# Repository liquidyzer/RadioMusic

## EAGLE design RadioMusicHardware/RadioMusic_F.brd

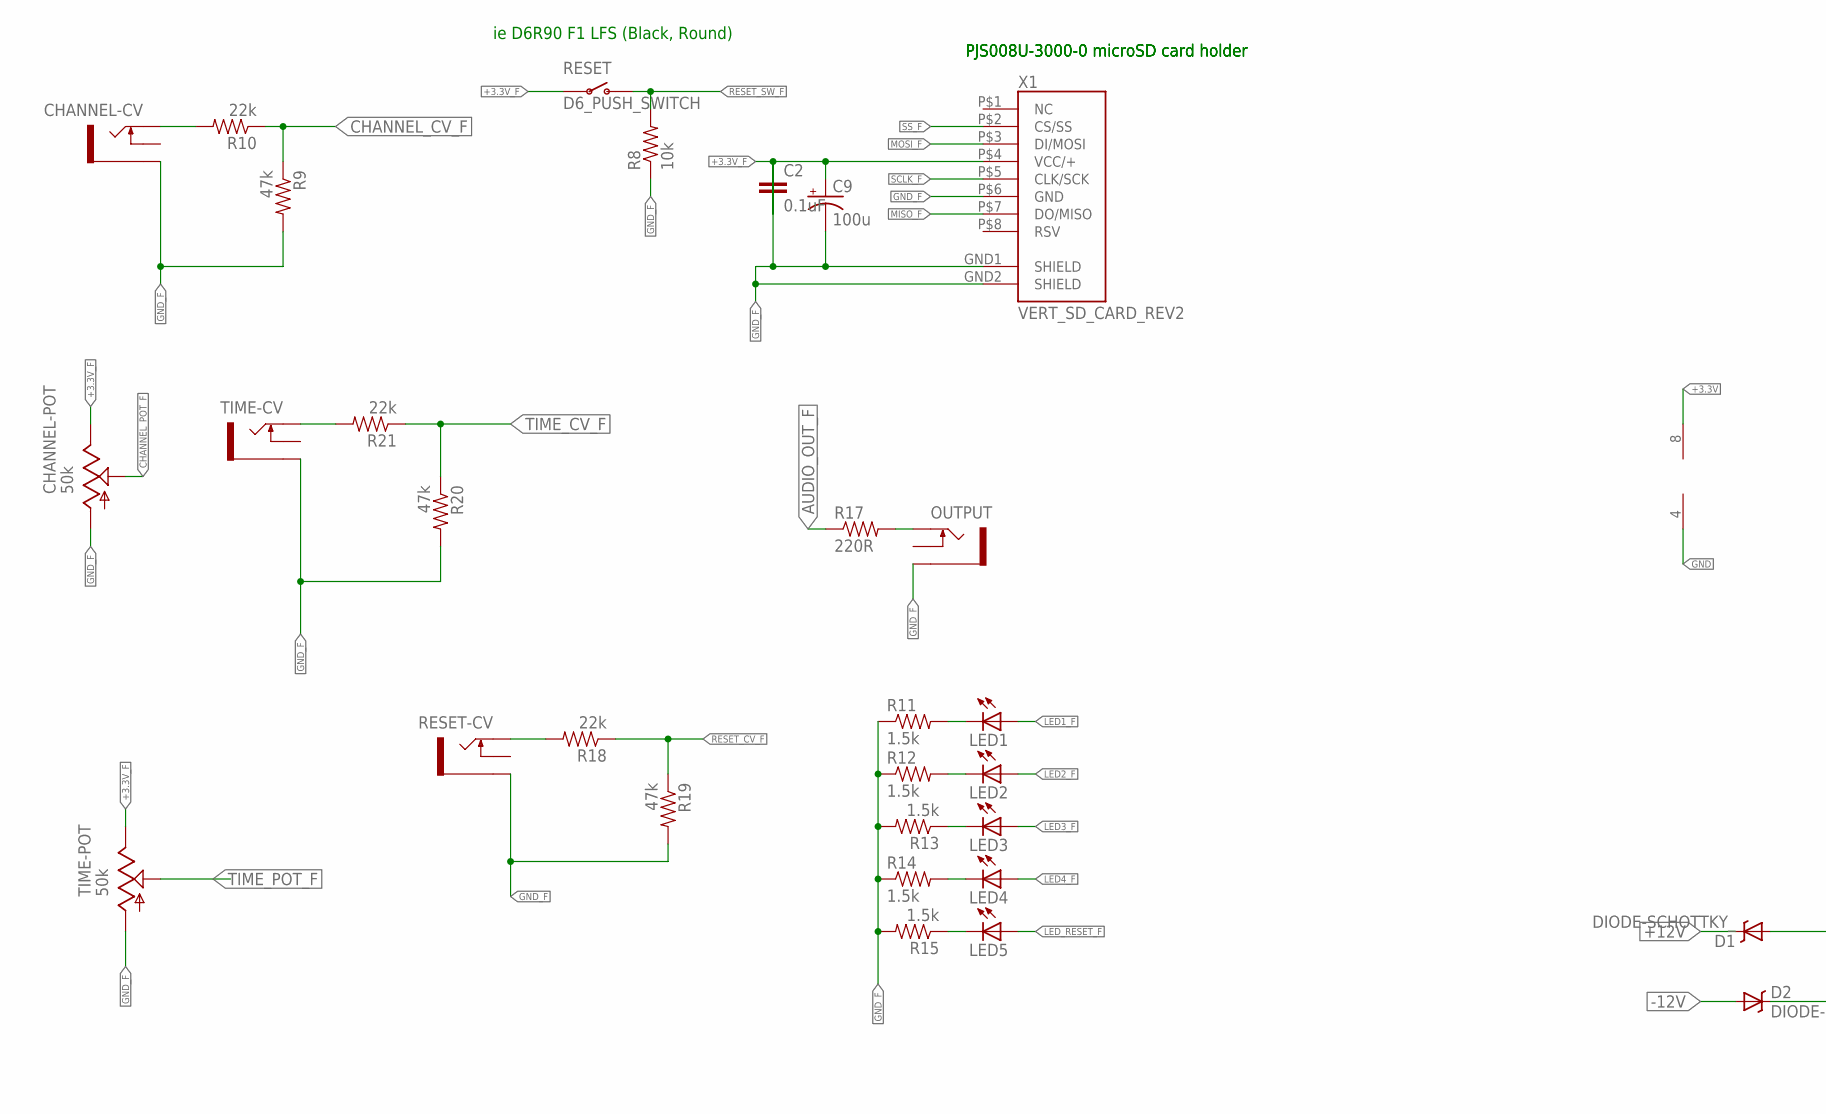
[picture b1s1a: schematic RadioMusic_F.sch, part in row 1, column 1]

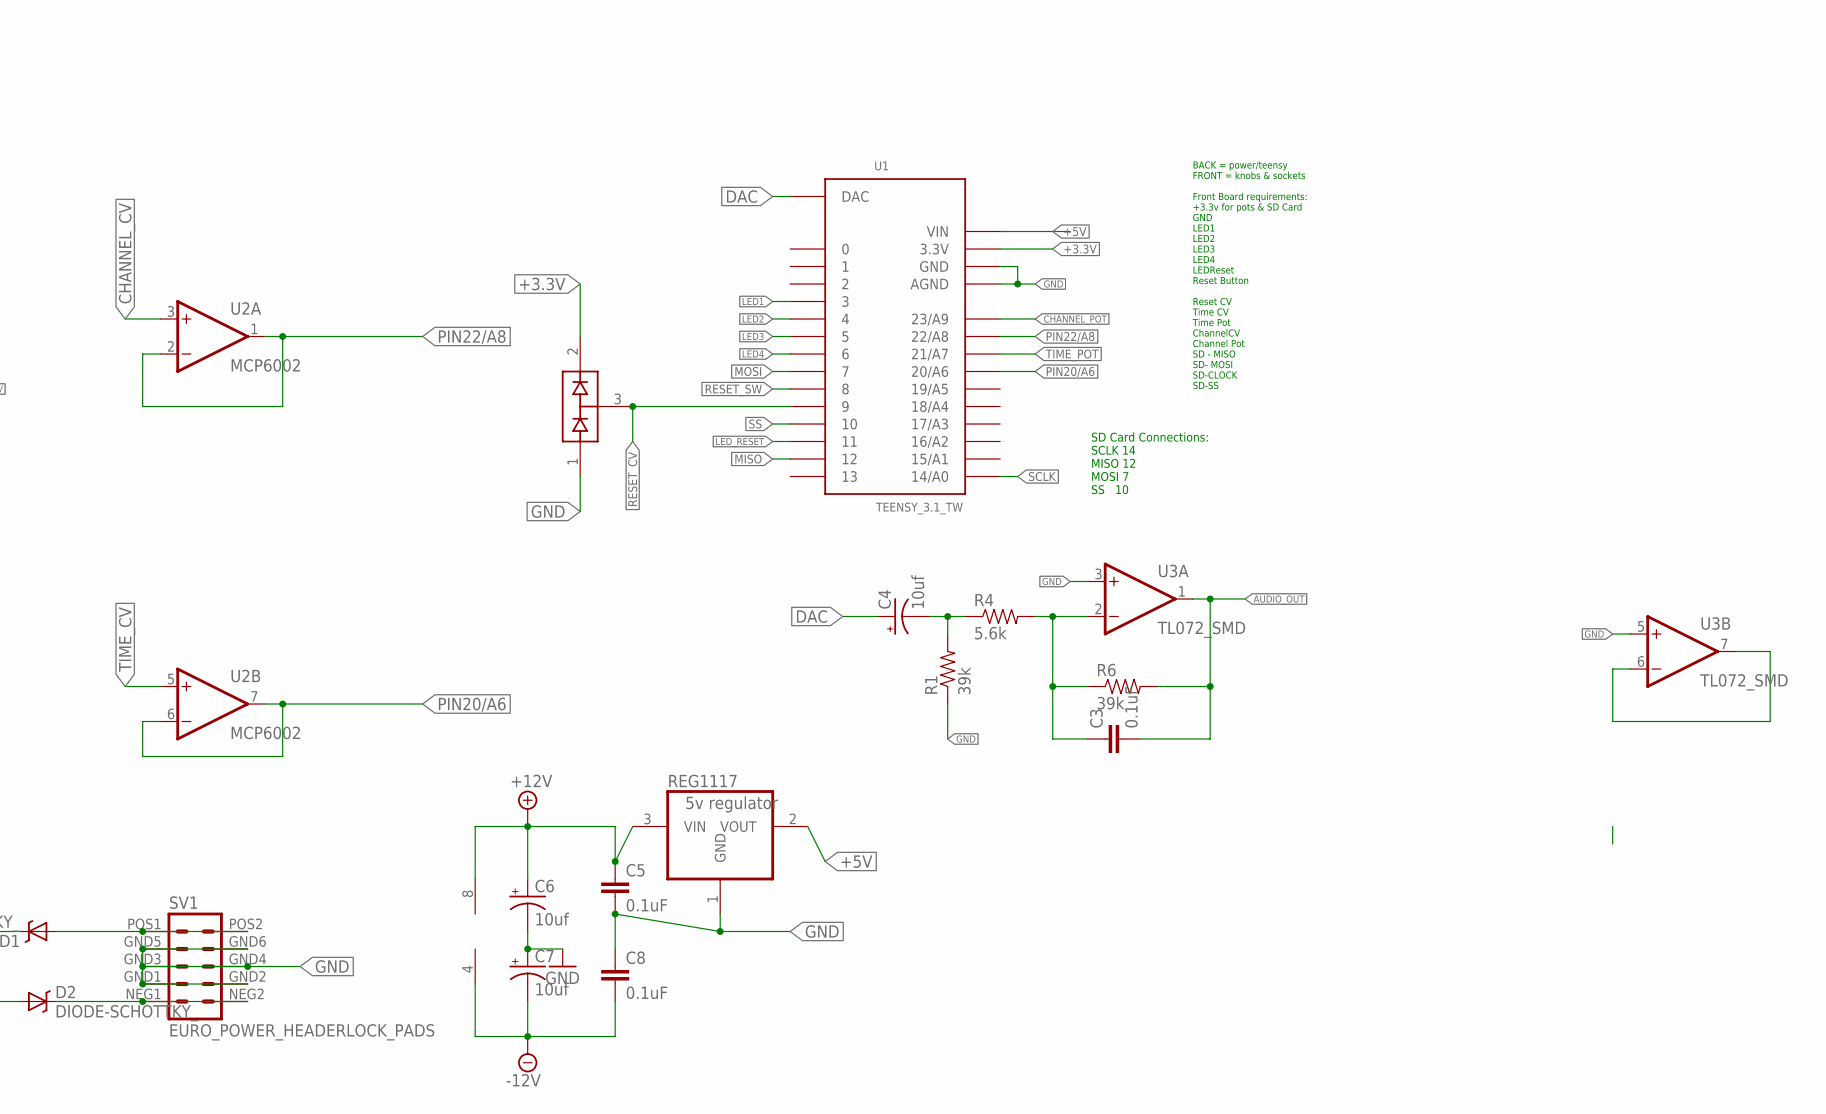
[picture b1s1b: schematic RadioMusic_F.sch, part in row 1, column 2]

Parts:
C2, C3, C5, C8: 0.1uF; 0603-CAP
C4: 10uf; PANASONIC_B
C6, C7: 10uf; PANASONIC_C
C9: 100u; PANASONIC_C
CHANNEL-CV: THONKICONNNEW; WQP-PJ301M-12_JACK
CHANNEL-POT: 50k; EVUF
D1, D2: DIODE-SCHOTTKY_; SMA-DIODE
D3: BAV99; SOT23
LED1, LED2, LED3, LED4, LED5: LED3MM
OUTPUT: THONKICONNNEW; WQP-PJ301M-12_JACK
R1, R6: 39k; 0603-RES
R4: 5.6k; 0603-RES
R8: 10k; 0603-RES
R9, R19, R20: 47k; 0603-RES
R10, R18, R21: 22k; 0603-RES
R11, R12, R13, R14, R15: 1.5k; 0603-RES
R17: 220R; 0603-RES
REG1117: 5v regulator; SOT223
RESET: D6_PUSH_SWITCH; D6_BUTTON_RND
RESET-CV: THONKICONNNEW; WQP-PJ301M-12_JACK
SV1: EURO_POWER_HEADERLOCK_PADS; EURO_PWR_HEADER_LOCK
TIME-CV: THONKICONNNEW; WQP-PJ301M-12_JACK
TIME-POT: 50k; EVUF
U1: TEENSY_3.1_TW
U2: MCP6002; SO08
U3: TL072_SMD; SO08
X1: VERT_SD_CARD_REV2; VERT_MICROSD_REV2

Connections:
+3.3V: D3.2 (C2), U1.3.3V, U2.8 (V+)
+3.3V_F: C2.2, C9.+, CHANNEL-POT.3 (E), RESET.P$3, RESET.P$4, TIME-POT.3 (E), X1.P$4 (VCC/+)
+5V: REG1117.2 (VOUT), U1.VIN
+12V: C5.1, C6.+, D1.C, REG1117.3 (VIN), U3.8 (V+)
-12V: C7.-, C8.2, D2.A, U3.4 (V-)
AUDIO_OUT: C3.2, R6.2, U3.1 (OUT)
AUDIO_OUT_F: R17.1
CHANNEL_CV: U2.3 (+IN)
CHANNEL_CV_F: R9.1, R10.1
CHANNEL_POT: U1.23/A9
CHANNEL_POT_F: CHANNEL-POT.2 (S)
DAC: C4.+, U1.DAC
GND: C5.2, C6.-, C7.+, C8.1, D3.1 (A1), REG1117.1 (GND), SV1.GND1 (4), SV1.GND2 (3), SV1.GND3 (6), SV1.GND4 (5), SV1.GND5 (8), SV1.GND6 (7), U1.AGND, U1.GND, U2.4 (V-), U3.3 (+IN), U3.5 (+IN)
GND_F: C2.1, C9.-, CHANNEL-CV.P$3_SLEEVE (SLEEVE), CHANNEL-POT.1 (A), OUTPUT.P$3_SLEEVE (SLEEVE), R8.1, R9.2, R11.1, R12.1, R13.2, R14.1, R15.2, R19.2, R20.2, RESET-CV.P$3_SLEEVE (SLEEVE), TIME-CV.P$3_SLEEVE (SLEEVE), TIME-POT.1 (A), X1.GND1 (SHIELD), X1.GND2 (SHIELD), X1.P$6 (GND)
LED1: U1.3
LED1_F: LED1.A
LED2: U1.4
LED2_F: LED2.A
LED3: U1.5
LED3_F: LED3.A
LED4: U1.6
LED4_F: LED4.A
LED_RESET: U1.11
LED_RESET_F: LED5.A
MISO: U1.12
MISO_F: X1.P$7 (DO/MISO)
MOSI: U1.7
MOSI_F: X1.P$3 (DI/MOSI)
unnamed: CHANNEL-CV.P$1_TIP (TIP), R10.2
unnamed: R21.2, TIME-CV.P$1_TIP (TIP)
unnamed: OUTPUT.P$1_TIP (TIP), R17.2
unnamed: C4.-, R1.2, R4.1
unnamed: C3.1, R4.2, R6.1, U3.2 (-IN)
unnamed: U3.6 (-IN), U3.7 (OUT)
unnamed: D1.A, SV1.POS1 (10), SV1.POS2 (9)
unnamed: D2.C, SV1.NEG1 (2), SV1.NEG2 (1)
unnamed: R18.2, RESET-CV.P$1_TIP (TIP)
unnamed: LED1.K (C), R11.2
unnamed: LED2.K (C), R12.2
unnamed: LED3.K (C), R13.1
unnamed: LED4.K (C), R14.2
unnamed: LED5.K (C), R15.1
PIN20/A6: U1.20/A6, U2.6 (-IN), U2.7 (OUT)
PIN22/A8: U1.22/A8, U2.1 (OUT), U2.2 (-IN)
RESET_CV: D3.3 (COM), U1.9
RESET_CV_F: R18.1, R19.1
RESET_SW: U1.8
RESET_SW_F: R8.2, RESET.P$1 (O), RESET.P$2 (O)
SCLK: U1.14/A0
SCLK_F: X1.P$5 (CLK/SCK)
SS: U1.10
SS_F: X1.P$2 (CS/SS)
TIME_CV: U2.5 (+IN)
TIME_CV_F: R20.1, R21.1
TIME_POT: U1.21/A7
TIME_POT_F: TIME-POT.2 (S)

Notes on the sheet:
ie D6R90 F1 LFS (Black, Round)
PJS008U-3000-0 microSD card holder
SD Card Connections: SCLK 14 MISO 12 MOSI 7 SS 10
BACK = power/teensy FRONT = knobs & sockets Front Board requirements: +3.3v for pots & SD Card GND LED1 LED2 LED3 LED4 LEDReset Reset Button Reset CV Time CV Time Pot ChannelCV Channel Pot SD - MISO SD- MOSI SD-CLOCK SD-SS

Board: 4 copper layers, 45 parts (2 on the bottom side), 30 nets, no tracks yet.

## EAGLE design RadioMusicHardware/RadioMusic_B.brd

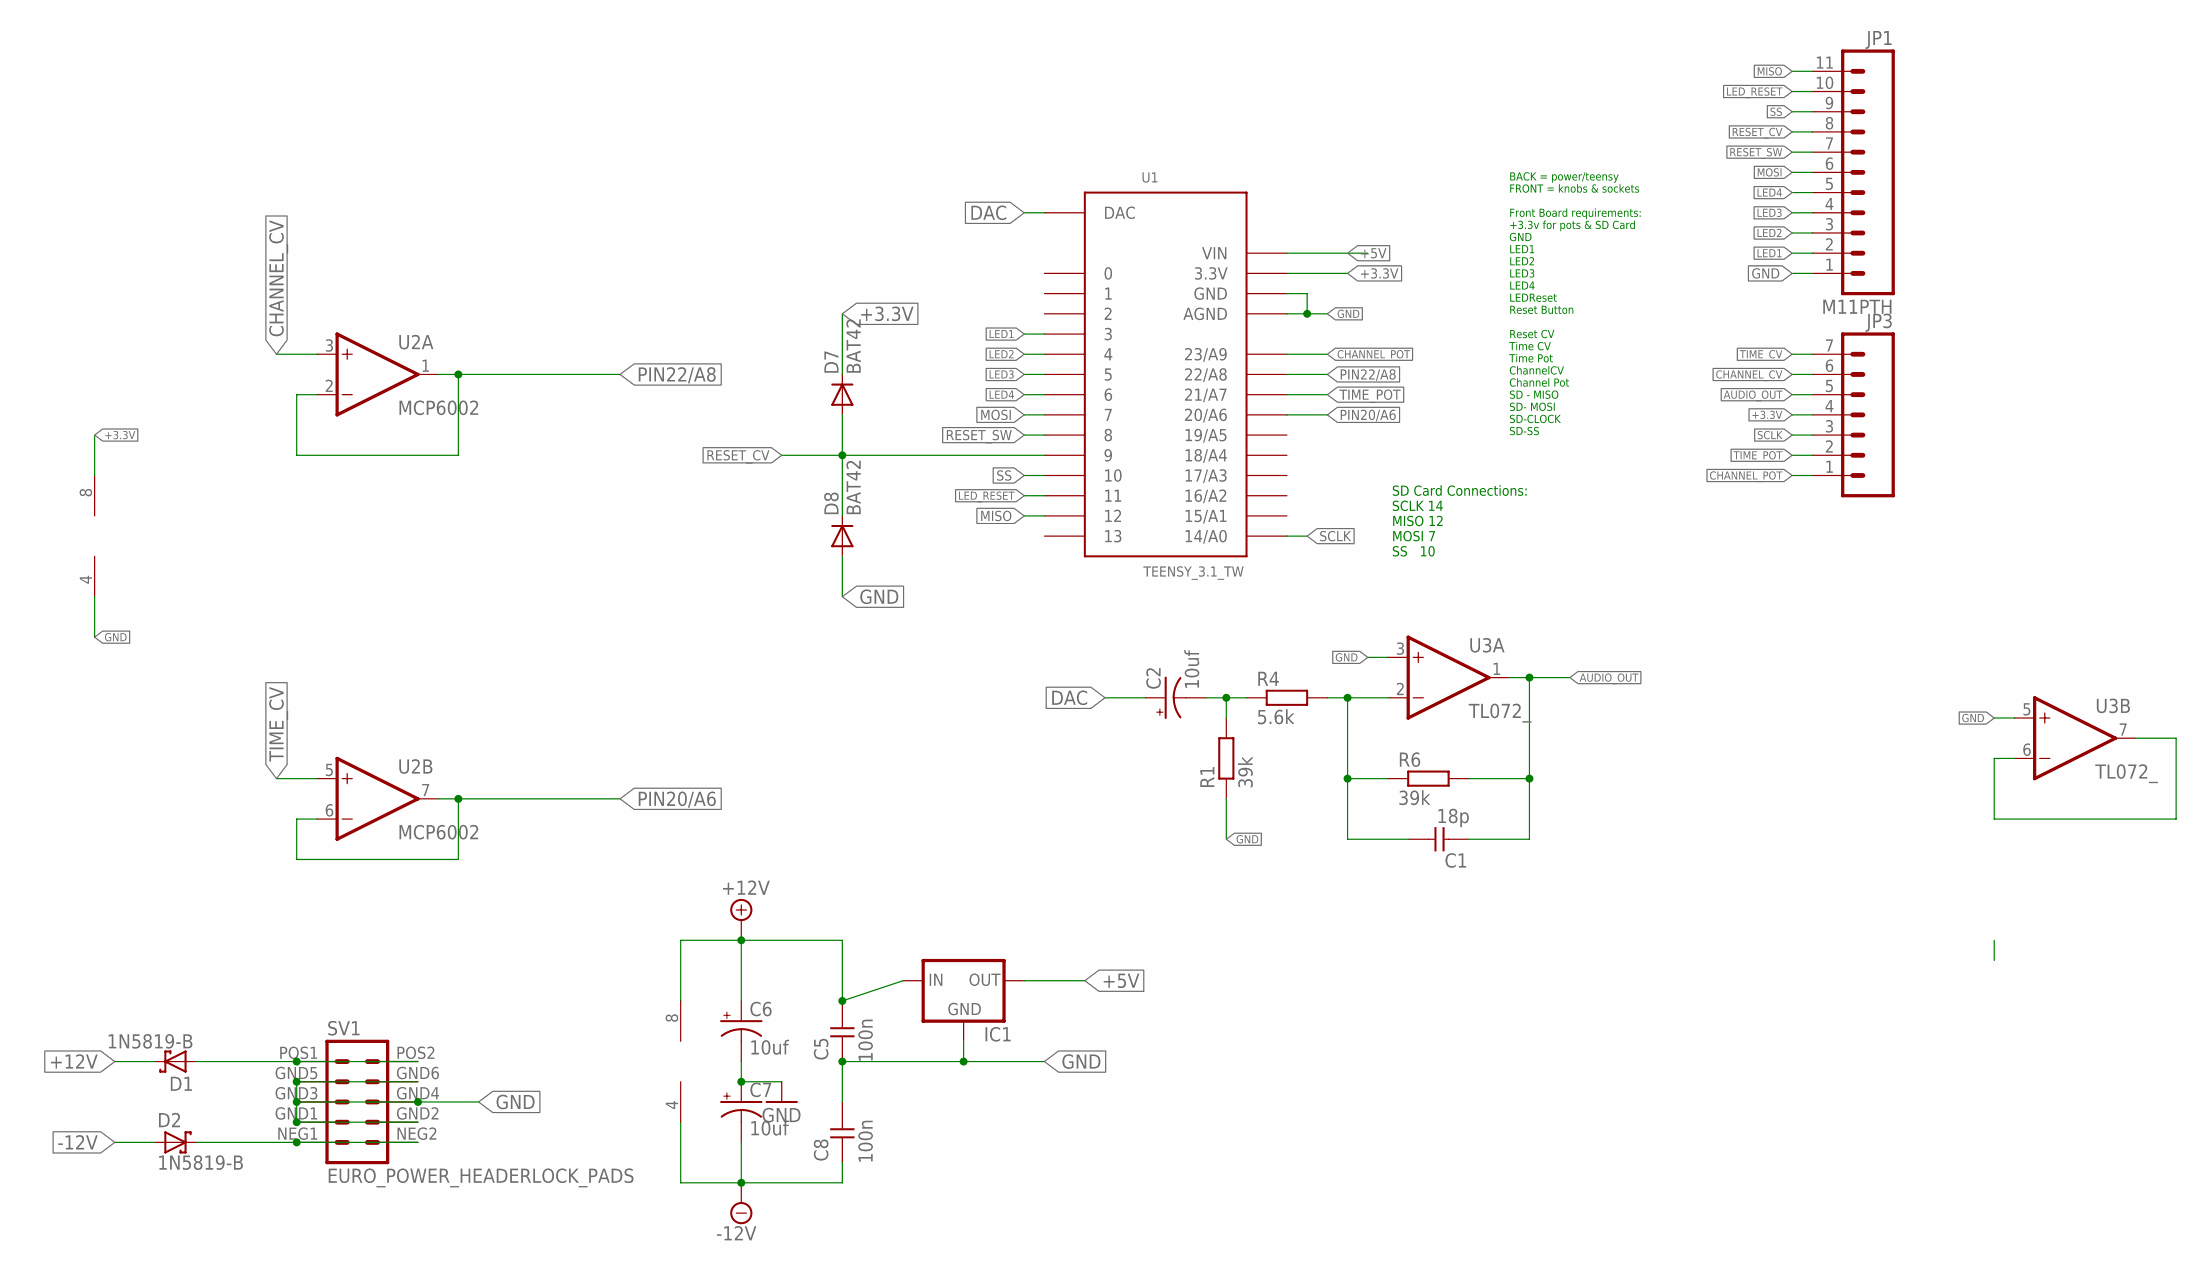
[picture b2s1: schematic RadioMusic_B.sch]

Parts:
C1: 18p; C050-024X044
C2, C6, C7: 10uf; CPOL-RADIAL-10UF-25V
C5, C8: 100n; C050-024X044
D1, D2: 1N5819-B; DO41-7.6
D7, D8: BAT42; DO35-7
IC1: 78LXX
JP1: M11PTH; 1X11
JP3: M07; 1X07
R1, R6: 39k; 7MM_RESISTOR
R4: 5.6k; 7MM_RESISTOR
SV1: EURO_POWER_HEADERLOCK_PADS; EURO_PWR_HEADER_LOCK
U1: TEENSY_3.1_TW
U2: MCP6002; DIL08
U3: TL072_; DIL08

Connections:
+3.3V: D7.C, JP3.4, U1.3.3V, U2.8 (V+)
+5V: IC1.OUT, U1.VIN
+12V: C5.1, C6.1 (+), D1.C, IC1.IN, U3.8 (V+)
-12V: C7.2 (-), C8.2, D2.A, U3.4 (V-)
AUDIO_OUT: C1.2, JP3.5, R6.2, U3.1 (OUT)
CHANNEL_CV: JP3.6, U2.3 (+IN)
CHANNEL_POT: JP3.1, U1.23/A9
DAC: C2.1 (+), U1.DAC
GND: C5.2, C6.2 (-), C7.1 (+), C8.1, D8.A, IC1.GND, JP1.1, SV1.GND1 (4), SV1.GND2 (3), SV1.GND3 (6), SV1.GND4 (5), SV1.GND5 (8), SV1.GND6 (7), U1.AGND, U1.GND, U2.4 (V-), U3.3 (+IN), U3.5 (+IN)
LED1: JP1.2, U1.3
LED2: JP1.3, U1.4
LED3: JP1.4, U1.5
LED4: JP1.5, U1.6
LED_RESET: JP1.10, U1.11
MISO: JP1.11, U1.12
MOSI: JP1.6, U1.7
unnamed: C2.2 (-), R1.2, R4.1
unnamed: D1.A, SV1.POS1 (10), SV1.POS2 (9)
unnamed: C1.1, R4.2, R6.1, U3.2 (-IN)
unnamed: D2.C, SV1.NEG1 (2), SV1.NEG2 (1)
unnamed: U3.6 (-IN), U3.7 (OUT)
PIN20/A6: U1.20/A6, U2.6 (-IN), U2.7 (OUT)
PIN22/A8: U1.22/A8, U2.1 (OUT), U2.2 (-IN)
RESET_CV: D7.A, D8.C, JP1.8, U1.9
RESET_SW: JP1.7, U1.8
SCLK: JP3.3, U1.14/A0
SS: JP1.9, U1.10
TIME_CV: JP3.7, U2.5 (+IN)
TIME_POT: JP3.2, U1.21/A7

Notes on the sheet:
SD Card Connections: SCLK 14 MISO 12 MOSI 7 SS 10
BACK = power/teensy FRONT = knobs & sockets Front Board requirements: +3.3v for pots & SD Card GND LED1 LED2 LED3 LED4 LEDReset Reset Button Reset CV Time CV Time Pot ChannelCV Channel Pot SD - MISO SD- MOSI SD-CLOCK SD-SS

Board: 4 copper layers, 22 parts (3 on the bottom side), 29 nets, no tracks yet.

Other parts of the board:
U$1: MOUNTING_HOLE
U$2: THONK_1CM_SCREENPRINT

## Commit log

2016-08-02 starting SMD needs layout
2016-08-02 everything fits on the board, but not properly placed or routed

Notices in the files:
RadioMusicHardware/RadioMusic_B.brd:
CC-BY-SA
RadioMusicHardware/RadioMusic_F.brd:
November 2015 CC-BY-SA
parts and their libraries:
SparkFun-Passives: Licensing: CC v3.0 Share-Alike You are welcome to use this library for commercial purposes.
